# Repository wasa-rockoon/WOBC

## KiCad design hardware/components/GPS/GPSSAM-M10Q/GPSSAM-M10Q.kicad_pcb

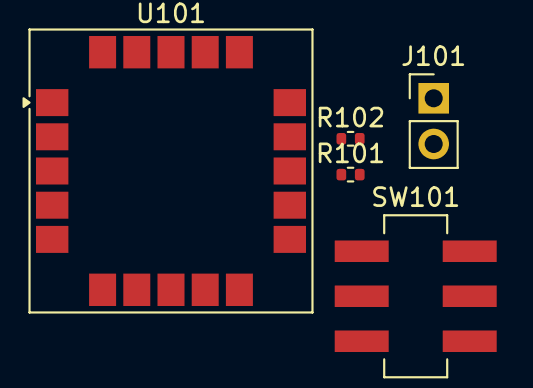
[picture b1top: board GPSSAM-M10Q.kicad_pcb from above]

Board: 2 copper layers, 5 parts (0 on the bottom side), 8 nets, no tracks yet.

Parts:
J101: Conn_01x02; PinHeader_1x02_P2.54mm_Vertical
R101, R102: 470; R_0402_1005Metric
SW101: SW_Push_DPDT; IS-2245S-G
U101: SAM-M10Q; ublox_SAM-M8Q

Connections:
GND: U101.1 (GND), U101.4 (GND), U101.5 (GND), U101.6 (GND), U101.10 (GND), U101.11 (GND), U101.15 (GND), U101.16 (GND), U101.20 (GND)
unnamed: J101.1, SW101.1 (A)
unnamed: J101.2, SW101.4 (A)
unnamed: R101.2, SW101.5 (B)
unnamed: R102.2, SW101.2 (B)
unnamed: R102.1, U101.14 (RXD)
unnamed: R101.1, U101.13 (TXD)
VDD: U101.2 (VCC_IO), U101.17 (VCC)

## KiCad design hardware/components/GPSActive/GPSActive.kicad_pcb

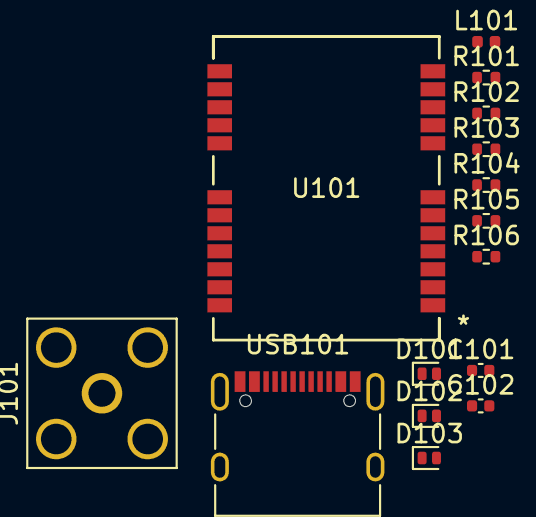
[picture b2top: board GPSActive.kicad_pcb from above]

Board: 2 copper layers, 15 parts (0 on the bottom side), 12 nets, no tracks yet.

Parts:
C101, C102: 100nF; C_0402_1005Metric
D101, D102, D103: 5V; D_SOD-882D
J101: SMA; SMA_Amphenol_132203-12_Horizontal
L101: 27nH, 300mA; L_0402_1005Metric
R101, R102: 22k; R_0402_1005Metric
R103: 10; R_0402_1005Metric
R104, R105: 33; R_0402_1005Metric
R106: 100K; R_0402_1005Metric
U101: NEO-M9N-00B; SMT_9N-00B_UBL
USB101: USB_C_Receptacle_USB2.0; USB_C_Receptacle_XKB_U262-16XN-4BVC11

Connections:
3V3: C102.2, R106.1, U101.23 (VCC)
/USB_D+: D102.2 (A2), U101.6 (USB_DP), USB101.A6 (D+), USB101.B6 (D+)
/USB_D-: D103.2 (A2), U101.5 (USB_DM), USB101.A7 (D-), USB101.B7 (D-)
GND: C101.2, C102.1, D101.1 (A1), D102.1 (A1), D103.1 (A1), J101.2 (Ext), R101.2, R102.2, R106.2, U101.10 (GND), U101.12 (GND), U101.13 (GND), U101.24 (GND), USB101.A1 (GND), USB101.A12 (GND), USB101.B1 (GND), USB101.B12 (GND), USB101.S1 (SHIELD)
GPS_ANT1: J101.1 (In), L101.1, U101.11 (RF_IN)
unnamed: C101.1, L101.2, R103.2
unnamed: D101.2 (A2), USB101.A4 (VBUS), USB101.A9 (VBUS), USB101.B4 (VBUS), USB101.B9 (VBUS)
unnamed: R104.2, U101.21 (RXD_/_SPI_MOSI)
unnamed: R105.2, U101.20 (TXD_/_SPI_MISO)
unnamed: R101.1, USB101.A5 (CC1)
unnamed: R102.1, USB101.B5 (CC2)
VCC_RF: R103.1, U101.9 (VCC_RF)

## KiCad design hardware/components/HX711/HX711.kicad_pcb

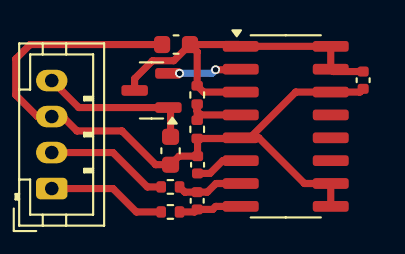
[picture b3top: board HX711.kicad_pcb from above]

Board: 2 copper layers, 12 parts (0 on the bottom side), 10 nets.

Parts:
C101, C104: 10uF; C_0603_1608Metric
C102, C103, C105: 0.1uF; C_0402_1005Metric
J101: Conn_01x04; JST_PH_B4B-PH-K_1x04_P2.00mm_Vertical
Q101: PNP; SOT-23
R101, R102: 100; R_0402_1005Metric
R103: 22k; R_0402_1005Metric
R104: 10k; R_0402_1005Metric
U101: HX711; SOP-16_3.9x9.9mm_P1.27mm

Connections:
GND: C101.2, C103.2, C104.2, C105.2, J101.3, R104.2, U101.5 (AGND), U101.9 (INB-), U101.10 (INB+), U101.14 (XI)
unnamed: J101.1, R101.1
unnamed: J101.2, R102.1
unnamed: C101.1, J101.4, Q101.1 (C)
unnamed: Q101.2 (B), U101.2 (BASE)
unnamed: C102.1, R101.2, U101.8 (INA+)
unnamed: C102.2, R102.2, U101.7 (INA-)
unnamed: C103.1, U101.6 (VBG)
unnamed: R103.2, R104.1, U101.4 (VFB)
VDD: C104.1, C105.1, Q101.3 (E), R103.1, U101.1 (VSUP), U101.3 (AVDD), U101.15 (RATE), U101.16 (DVDD)

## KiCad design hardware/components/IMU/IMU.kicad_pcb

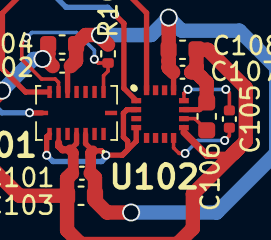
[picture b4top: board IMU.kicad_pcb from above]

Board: 2 copper layers, 11 parts (0 on the bottom side), 8 nets.

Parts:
C101, C102, C107: 100nF; C_0402_1005Metric
C103, C104, C108: 10μF; C_0603_1608Metric
C105: 0.22μF; C_0402_1005Metric
C106: 4.7μF; C_0603_1608Metric
R101: 4.7K; R_0402_1005Metric
U101: BMI088
U102: QMC5883L; _HMC5883L

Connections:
/I2C_SCL: U101.8 (SCL/SCK), U102.1 (SCL)
/I2C_SDA: U101.9 (SDA/SDI), U102.16 (SDA)
GND: C101.2, C102.2, C103.2, C104.2, C106.2, C107.2, C108.2, U101.4 (GNDA), U101.6 (GNDIO), U102.9 (GND), U102.11 (GND)
unnamed: R101.1, U101.10 (SDO2), U101.15 (SDO1)
unnamed: C106.1, U102.10 (C1)
unnamed: C105.1, U102.12 (SETC)
unnamed: C105.2, U102.8 (STEP)
VDD: C101.1, C102.1, C103.1, C104.1, C107.1, C108.1, R101.2, U101.3 (VDD), U101.7 (PS), U101.11 (VDDIO), U102.2 (VDD), U102.4 (S1), U102.13 (VDDIO)

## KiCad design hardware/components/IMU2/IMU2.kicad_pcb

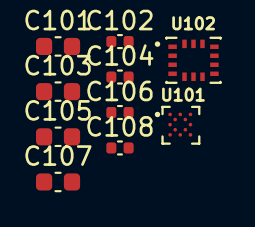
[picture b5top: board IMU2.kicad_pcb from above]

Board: 2 copper layers, 10 parts (0 on the bottom side), 4 nets, no tracks yet.

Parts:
C101, C103, C105, C107: 10uF; C_0603_1608Metric
C102, C104, C106, C108: 100nF; C_0402_1005Metric
U101: BMM150; XDCR_BMM150
U102: BMI270; XDCR_BMI270

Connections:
/SCL: U101.A3 (SCK), U102.13 (SCX)
/SDA: U101.B4 (SDI), U102.14 (SDX)
GND: C101.2, C102.2, C103.2, C104.2, C105.2, C106.2, C107.2, C108.2, U101.A5 (CSB), U101.C1 (SDO), U101.C5 (GND), U101.E1 (GND__1), U101.E3 (GND__2), U102.1 (SDO), U102.6 (GNDIO), U102.7 (GND)
VDD: C101.1, C102.1, C103.1, C104.1, C105.1, C106.1, C107.1, C108.1, U101.A1 (PS), U101.B2 (VDDIO), U101.E5 (VDD), U102.2 (ASDX), U102.3 (ASCX), U102.5 (VDDIO), U102.8 (VDD), U102.12 (CSB)

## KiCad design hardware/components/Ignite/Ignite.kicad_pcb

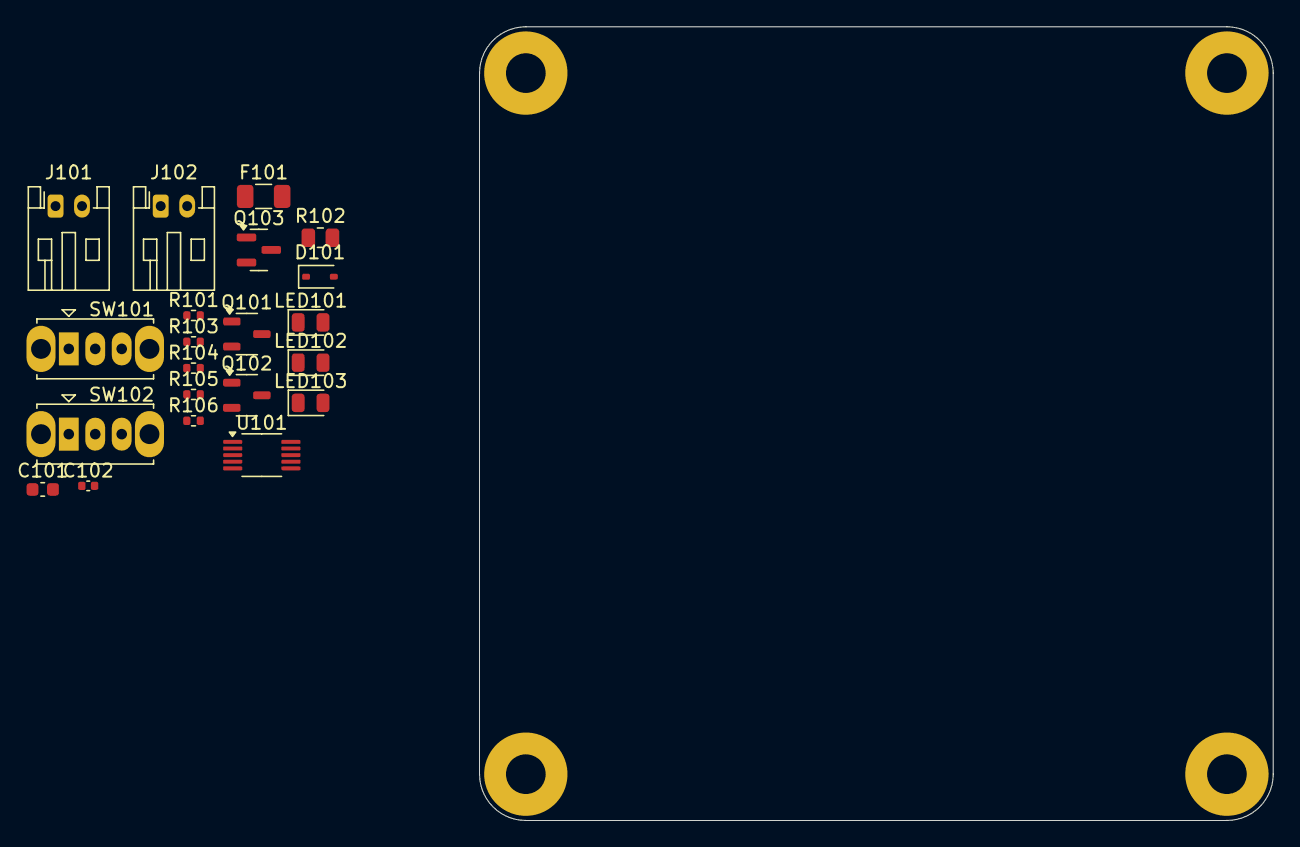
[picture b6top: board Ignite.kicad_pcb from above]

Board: 2 copper layers, 60.0 x 60.0 mm, 21 parts (0 on the bottom side), 17 nets, no tracks yet.

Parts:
C101: 10uF; C_0603_1608Metric
C102: 100nF; C_0402_1005Metric
D101: D_Schottky; D_SOD-323
F101: Polyfuse; Fuse_1206_3216Metric
J101: LiPo 1 Cell; JST_PH_S2B-PH-K_1x02_P2.00mm_Horizontal
J102: IGNITER; JST_PH_S2B-PH-K_1x02_P2.00mm_Horizontal
LED101: NMOS1; LED_0805_2012Metric
LED102: NPN; LED_0805_2012Metric
LED103: NMOS2; LED_0805_2012Metric
Q101, Q102: Q_NMOS_GSD; SOT-23-3
Q103: Q_NPN_BEC; SOT-23
R101, R104, R105: 510; R_0402_1005Metric
R102: 50mΩ; R_0805_2012Metric
R103: 10k; R_0402_1005Metric
R106: 1k; R_0402_1005Metric
SW101, SW102: Power Switch; SW_Slide_SPDT_Straight_CK_OS102011MS2Q
U101: INA226; VSSOP-10_3x3mm_P0.5mm

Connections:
/Alert: D101.1 (K), R101.1
/Check1: Q101.1 (G), R103.2, R104.1
/I2C_SCL: U101.1 (A1), U101.5 (SCL)
/VS: C101.1, C102.1, U101.2 (A0), U101.6 (VS)
GND: C101.2, C102.2, J101.2, LED101.1 (K), Q102.2 (S), Q103.3 (E), U101.7 (GND)
unnamed: D101.2 (A), Q101.3 (D), SW102.2 (B)
unnamed: J101.1, SW101.2 (B)
unnamed: J102.1, R102.1, U101.9 (Vin-)
unnamed: J102.2, Q102.3 (D), R105.2
unnamed: LED101.2 (A), R101.2
unnamed: LED102.2 (A), R104.2
unnamed: LED102.1 (K), Q103.1 (C)
unnamed: LED103.2 (A), R105.1
unnamed: F101.2, Q101.2 (S), R103.1
unnamed: Q103.2 (B), R106.2
unnamed: F101.1, SW101.3 (C)
unnamed: R102.2, SW102.3 (C), U101.8 (Vbus), U101.10 (Vin+)
